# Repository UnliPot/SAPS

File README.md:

# Semi-Automatic Processing Station

the complete guide for home developing station.

Working on: user guide, build guide and production guide -> will be added soon

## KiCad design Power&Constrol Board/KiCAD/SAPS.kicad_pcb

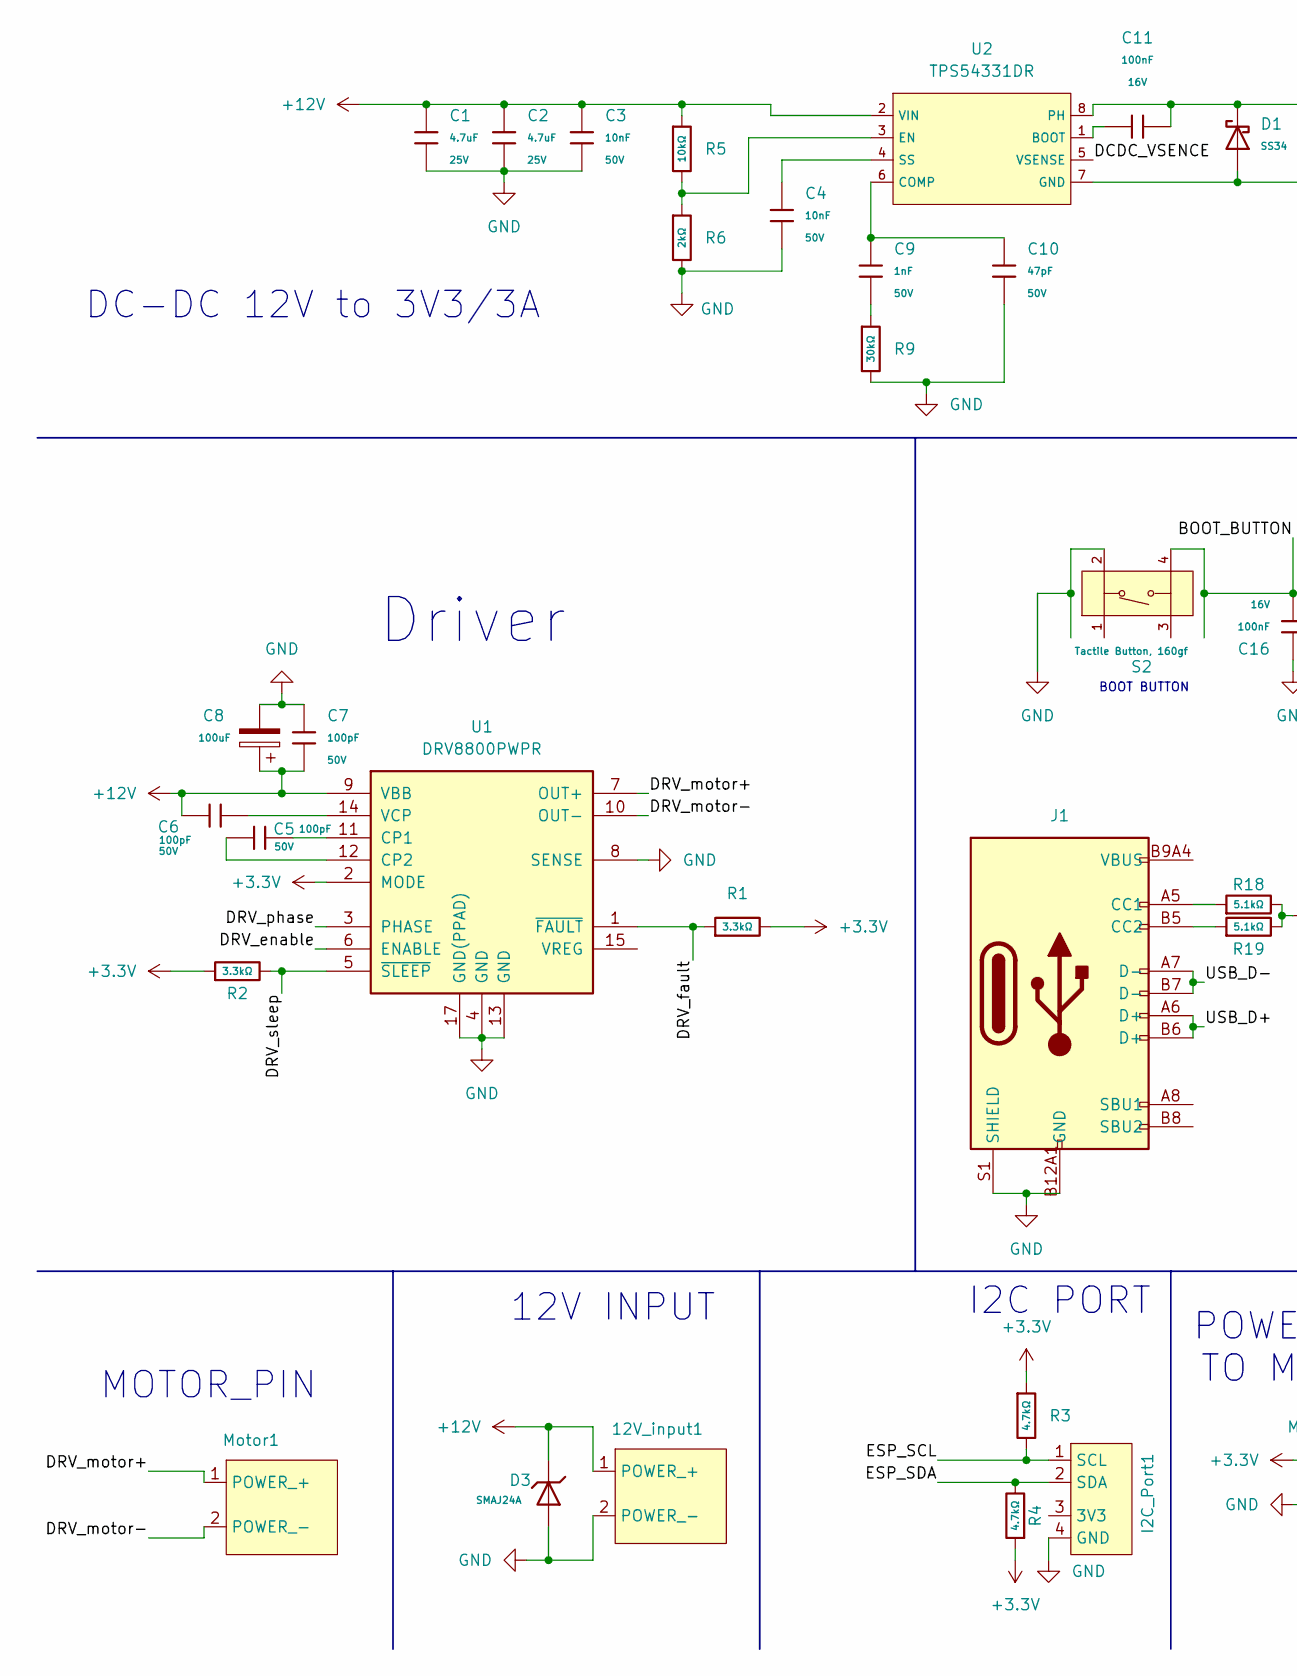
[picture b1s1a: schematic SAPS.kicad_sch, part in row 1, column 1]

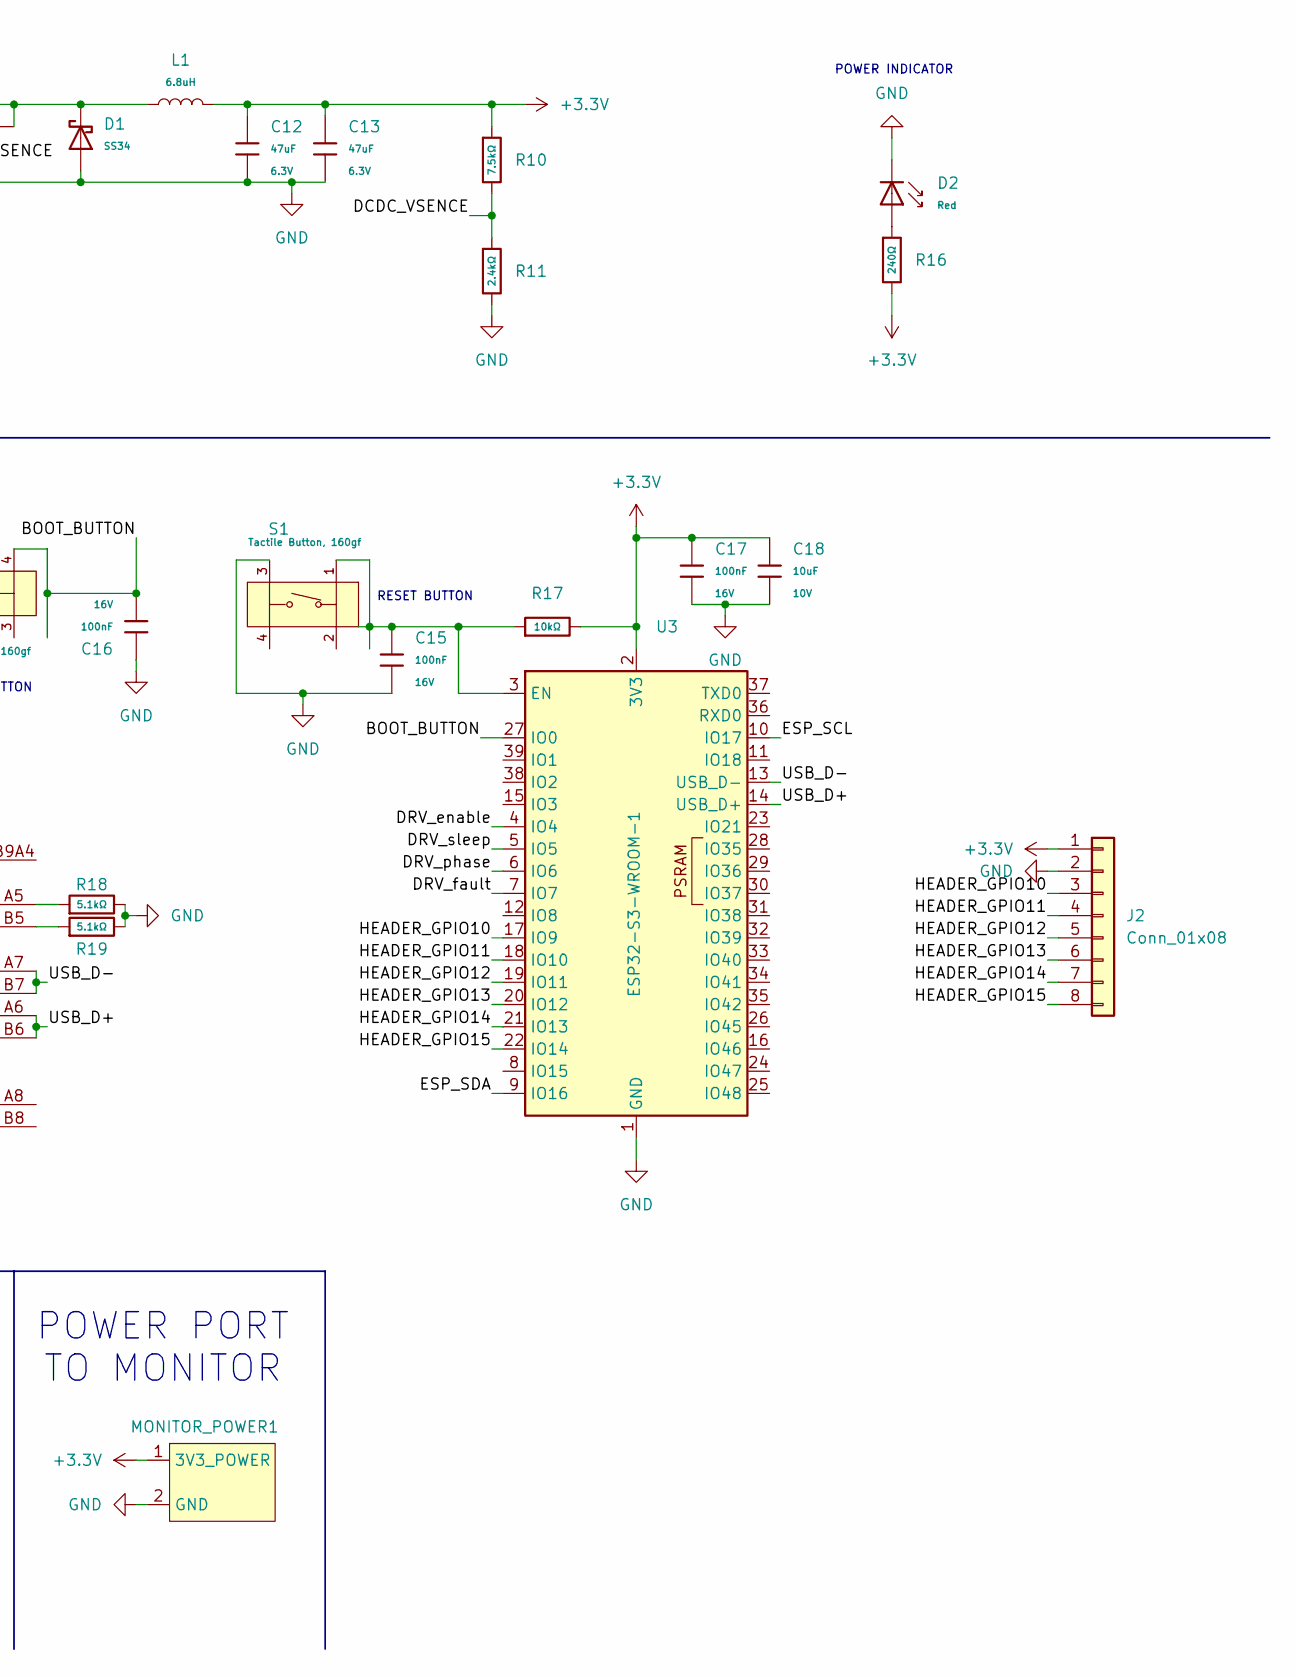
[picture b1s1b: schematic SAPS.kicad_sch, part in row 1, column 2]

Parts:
12V_input1: TerminalBlock_4Ucon_1x02_P3.50mm_Horizontal
C1, C2: 4.7uF; C_0805; Voltage Rated 25V; Tolerance ±10%; Part CL21A475KAQNNNE; LCSC C1779
C3, C4: 10nF; C_0402; Voltage Rated 50V; Tolerance ±10%; Part CL05B103KB5NNNC; LCSC C15195
C5, C6, C7: 100pF; C_0603; Voltage Rated 50V; Tolerance ±5%; Part CL10C101JB8NNNC; LCSC C14858
C8: 100uF; CP_Radial_D5.0mm_P2.00mm
C9: 1nF; C_0603; Voltage Rated 50V; Tolerance ±10%; Part CL10B102KB8NNNC; LCSC C1588
C10: 47pF; C_0603; Voltage Rated 50V; Tolerance ±5%; Part CL10C470JB8NNNC; LCSC C1671
C11, C15, C16, C17: 100nF; C_0402; Voltage Rated 16V; Tolerance ±10%; Part CL05B104KO5NNNC; LCSC C1525
C12, C13: 47uF; C_0805; Voltage Rated 6.3V; Tolerance ±20%; Part CL21A476MQYNNNE; LCSC C16780
C18: 10uF; C_0603; Voltage Rated 10V; Tolerance ±10%; Part CL10A106KP8NNNC; LCSC C19702
D1: SS34; D_SMA; Forward Voltage (Vf@If) 550mV@3A; Reverse Voltage (Vr) 40V; Part SS34; LCSC C8678
D2: Red; D_0603; Part KT-0603R; LCSC C2286
D3: SMAJ24A; D_SMA; Part SMAJ24A; LCSC C19077541
I2C_Port1: JST_XH_B4B-XH-A_1x04_P2.50mm_Vertical
J1: Connector, USB-TYPE-C-16P; TYPE-C-SMD_HX-TYPE-C-16PIN; LCSC C2927039
J2: Conn_01x08; PinHeader_1x08_P2.00mm_Vertical
L1: 6.8uH; L_SMD,12.3x12.3mm; LCSC C10149
MONITOR_POWER1: JST_XH_B2B-XH-A_1x02_P2.50mm_Vertical
Motor1: TerminalBlock_4Ucon_1x02_P3.50mm_Horizontal
R1, R2: 3.3kΩ; R_0603; Overload Voltage (Max) 75V; Tolerance ±1%; Part 0603WAF3301T5E; LCSC C22978
R3, R4: 4.7kΩ; R_0603; Overload Voltage (Max) 75V; Tolerance ±1%; Part 0603WAF4701T5E; LCSC C23162
R5, R17: 10kΩ; R_0603; Overload Voltage (Max) 75V; Tolerance ±1%; Part 0603WAF1002T5E; LCSC C25804
R6: 2kΩ; R_0603; Overload Voltage (Max) 75V; Tolerance ±1%; Part 0603WAF2001T5E; LCSC C22975
R9: 30kΩ; R_0603; Overload Voltage (Max) 75V; Tolerance ±1%; Part 0603WAF3002T5E; LCSC C22984
R10: 7.5kΩ; R_0603; Overload Voltage (Max) 75V; Tolerance ±1%; Part 0603WAF7501T5E; LCSC C23234
R11: 2.4kΩ; R_0603; Overload Voltage (Max) 75V; Tolerance ±1%; Part 0603WAF2401T5E; LCSC C22940
R16: 240Ω; R_0603; Overload Voltage (Max) 75V; Tolerance ±1%; Part 0603WAF2400T5E; LCSC C23350
R18, R19: 5.1kΩ; R_0603; Overload Voltage (Max) 75V; Tolerance ±1%; Part 0603WAF5101T5E; LCSC C23186
S1, S2: Tactile Button, 160gf; SW-SMD_4P-L5.1-W5.1-P3.70-LS6.5-TL-2; Voltage Rating (Dc) 12V; Part TS-1187A-B-A-B; LCSC C318884
U1: DRV8800PWPR; TSSOP-16-1EP_4.4x5mm_P0.65mm_EP3x3mm_ThermalVias; LCSC C32579
U2: TPS54331DR; SOIC-8_L5.0-W4.0-P1.27-LS6.0-BL; Output Voltage 0.8V~25V; Input Voltage 3.5V~28V; Part TPS54331DR; LCSC C9865
U3: ESP32-S3-WROOM-1; ESP32-S3-WROOM-1U; LCSC C2980297

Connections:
+3.3V: C12.1, C13.1, C17.1, C18.1, J2.1, L1.2, MONITOR_POWER1.1 (3V3_POWER), R1.2, R2.1, R3.1, R4.1, R10.1, R16.2, R17.2, U1.2 (MODE), U3.2 (3V3); also elsewhere on the board
+12V: 12V_input1.1 (POWER_+), C1.1, C2.1, C3.1, C6.1, C7.2, C8.1, D3.1, R5.1, U1.9 (VBB), U2.2 (VIN)
/BOOT_BUTTON: C16.2, S2.4 (D), U3.27 (IO0)
/DCDC_VSENCE: R10.2, R11.1, U2.5 (VSENSE)
/DRV_enable: U1.6 (ENABLE), U3.4 (IO4)
/DRV_fault: R1.1, U1.1 (~FAULT), U3.7 (IO7)
/DRV_motor+: Motor1.1 (POWER_+), U1.7 (OUT+)
/DRV_motor-: Motor1.2 (POWER_-), U1.10 (OUT-)
/DRV_phase: U1.3 (PHASE), U3.6 (IO6)
/DRV_sleep: R2.2, U1.5 (~SLEEP), U3.5 (IO5)
/ESP_SCL: I2C_Port1.1 (SCL), R3.2, U3.10 (IO17); also elsewhere on the board
/ESP_SDA: I2C_Port1.2 (SDA), R4.2, U3.9 (IO16); also elsewhere on the board
/HEADER_GPIO10: J2.3, U3.17 (IO9)
/HEADER_GPIO11: J2.4, U3.18 (IO10)
/HEADER_GPIO12: J2.5, U3.19 (IO11)
/HEADER_GPIO13: J2.6, U3.20 (IO12)
/HEADER_GPIO14: J2.7, U3.21 (IO13)
/HEADER_GPIO15: J2.8, U3.22 (IO14)
/USB_D+: J1.A6 (D+), J1.B6 (D+), U3.14 (USB_D+)
/USB_D-: J1.A7 (D-), J1.B7 (D-), U3.13 (USB_D-)
GND: 12V_input1.2 (POWER_-), C1.2, C2.2, C3.2, C4.2, C7.1, C8.2, C10.2, C12.2, C13.2, C15.2, C16.1, C17.2, C18.2, D1.2, D2.1, D3.2, I2C_Port1.4 (GND), J1.A12B1 (GND), J1.B12A1 (GND), J1.S1 (SHIELD), J2.2, MONITOR_POWER1.2 (GND), R6.2, R9.2, R11.2, R18.2, R19.2, S1.3 (C), S2.2 (B), U1.4 (GND), U1.8 (SENSE), U1.13 (GND), U1.17 (GND(PPAD)), U2.7 (GND), U3.1 (GND), U3.40 (GND), U3.41 (GND); also elsewhere on the board
unnamed: C9.2, R9.1
unnamed: D2.2, R16.1
unnamed: J1.A5 (CC1), R18.1
unnamed: J1.B5 (CC2), R19.1
unnamed: J1.A9B4 (VBUS), J1.B9A4 (VBUS)
unnamed: C15.1, R17.1, S1.1 (A), U3.3 (EN)
unnamed: C5.1, U1.11 (CP1)
unnamed: C5.2, U1.12 (CP2)
unnamed: C6.2, U1.14 (VCP)
unnamed: C11.1, U2.1 (BOOT)
unnamed: C9.1, C10.1, U2.6 (COMP)
unnamed: R5.2, R6.1, U2.3 (EN)
unnamed: C11.2, D1.1, L1.1, U2.8 (PH)
unnamed: C4.1, U2.4 (SS)

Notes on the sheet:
POWER INDICATOR
POWER PORT TO MONITOR
RESET BUTTON
Driver
I2C PORT
BOOT BUTTON
12V INPUT
DC-DC 12V to 3V3/3A
MOTOR_PIN

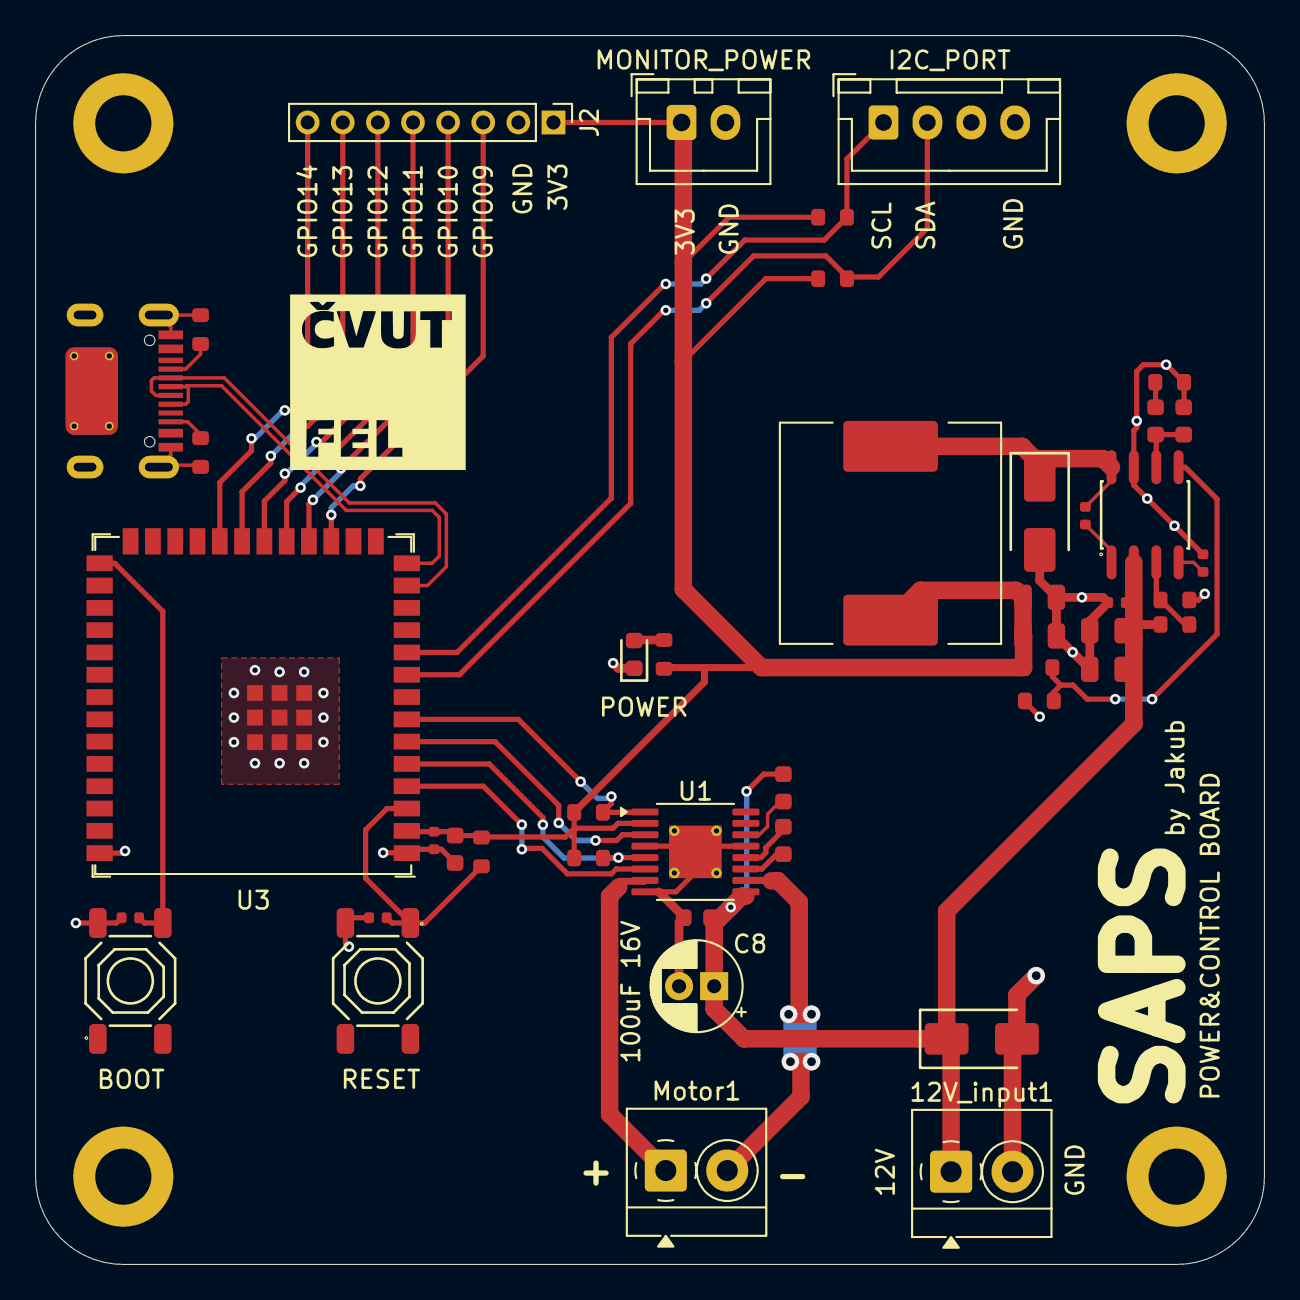
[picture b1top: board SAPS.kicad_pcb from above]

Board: 2 copper layers, 70.0 x 70.0 mm, 45 parts (0 on the bottom side), 35 nets.

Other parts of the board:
I2C_PORT: JST_XH_B4B-XH-A_1x04_P2.50mm_Vertical
MONITOR_POWER: JST_XH_B2B-XH-A_1x02_P2.50mm_Vertical

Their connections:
+3.3V: MONITOR_POWER.1 (3V3_POWER); also elsewhere on the board
/ESP_SCL: I2C_PORT.1 (SCL); also elsewhere on the board
/ESP_SDA: I2C_PORT.2 (SDA); also elsewhere on the board
GND: I2C_PORT.4 (GND), MONITOR_POWER.2 (GND); also elsewhere on the board

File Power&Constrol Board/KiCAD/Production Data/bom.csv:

Designator,Footprint,Quantity,Value,LCSC Part #
"12V_INPUT1, MOTOR1",TerminalBlock_4Ucon_1x02_P3.50mm_Horizontal,2,~,
"C1, C2",C_0805,2,4.7uF,C1779
C10,C_0603,1,47pF,C1671
"C11, C15, C16, C17",C_0402,4,100nF,C1525
"C12, C13",C_0805,2,47uF,C16780
C18,C_0603,1,10uF,C19702
"C3, C4",C_0402,2,10nF,C15195
"C5, C6, C7",C_0603,3,100pF,C14858
C8,CP_Radial_D5.0mm_P2.00mm,1,100uF,
C9,C_0603,1,1nF,C1588
D1,D_SMA,1,SS34,C8678
D2,D_0603,1,Red,C2286
D3,D_SMA,1,SMAJ24A,C19077541
I2C_PORT,JST_XH_B4B-XH-A_1x04_P2.50mm_Vertical,1,~,
J1,TYPE-C-SMD_HX-TYPE-C-16PIN,1,"Connector, USB-TYPE-C-16P",C2927039
J2,PinHeader_1x08_P2.00mm_Vertical,1,Conn_01x08,
L1,"L_SMD,12.3x12.3mm",1,6.8uH,C10149
MONITOR_POWER,JST_XH_B2B-XH-A_1x02_P2.50mm_Vertical,1,~,
"R1, R2",R_0603,2,3.3kΩ,C22978
R10,R_0603,1,7.5kΩ,C23234
R11,R_0603,1,2.4kΩ,C22940
R16,R_0603,1,240Ω,C23350
"R17, R5",R_0603,2,10kΩ,C25804
"R18, R19",R_0603,2,5.1kΩ,C23186
"R3, R4",R_0603,2,4.7kΩ,C23162
R6,R_0603,1,2kΩ,C22975
R9,R_0603,1,30kΩ,C22984
"S1, S2",SW-SMD_4P-L5.1-W5.1-P3.70-LS6.5-TL-2,2,"Tactile Button, 160gf",C318884
U1,TSSOP-16-1EP_4.4x5mm_P0.65mm_EP3x3mm_ThermalVias,1,DRV8800PWPR,C32579
U2,SOIC-8_L5.0-W4.0-P1.27-LS6.0-BL,1,TPS54331DR,C9865
U3,ESP32-S3-WROOM-1U,1,ESP32-S3-WROOM-1,C2980297

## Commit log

2025-05-23 Code and files
2025-05-23 Readme updated
2025-05-23 uprated readme
